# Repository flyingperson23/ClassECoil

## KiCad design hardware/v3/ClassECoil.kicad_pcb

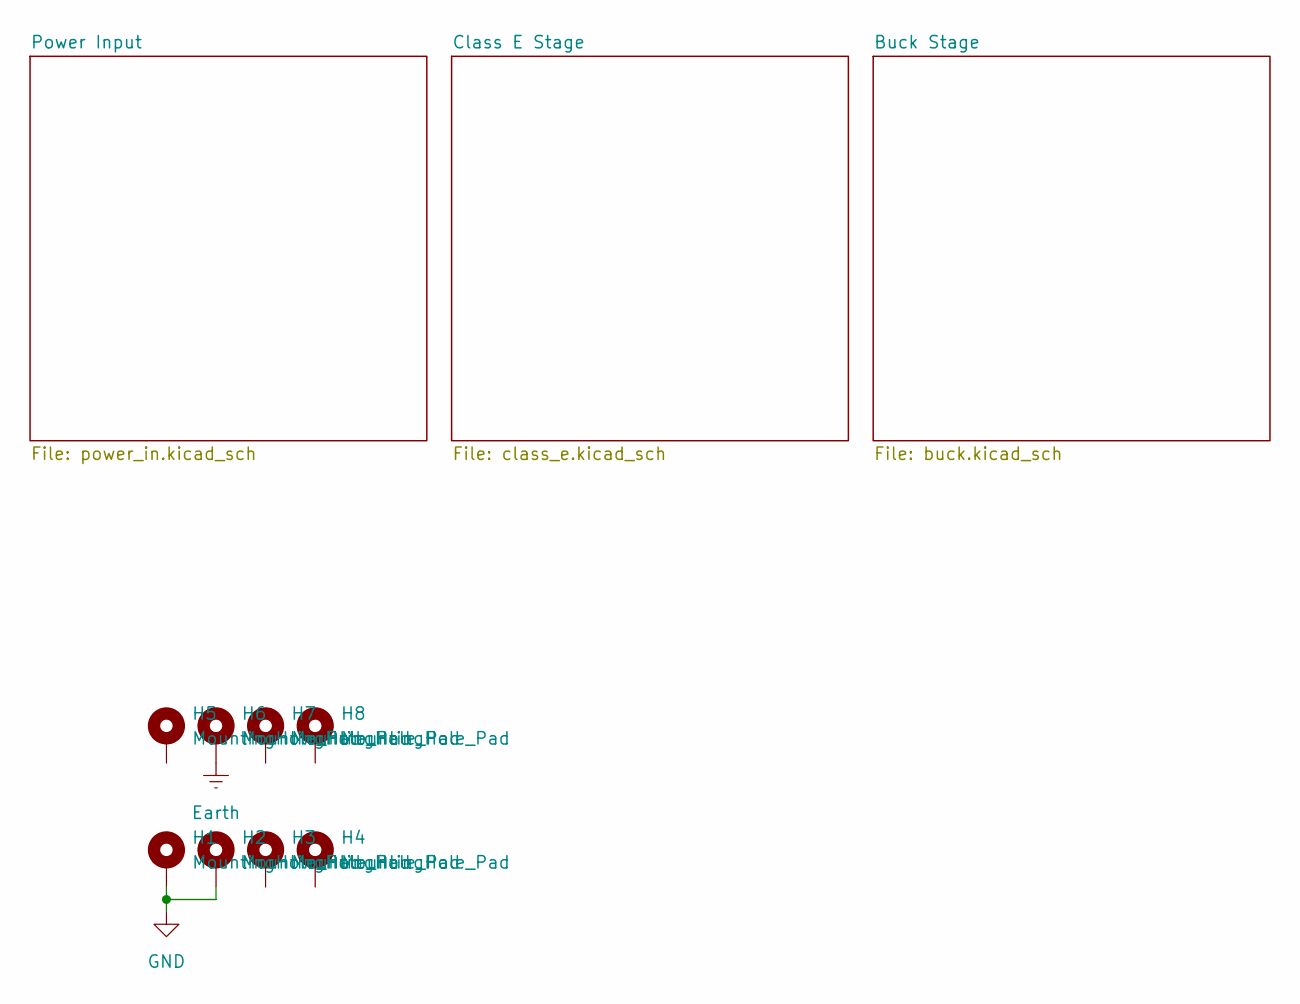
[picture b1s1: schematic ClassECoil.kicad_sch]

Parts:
H1, H2, H3, H4, H5, H6, H7, H8: MountingHole_Pad; MountingHole_3.2mm_M3_Pad_Via

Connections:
Earth: H6.1; also elsewhere on the board
GND: H1.1, H2.1; also elsewhere on the board

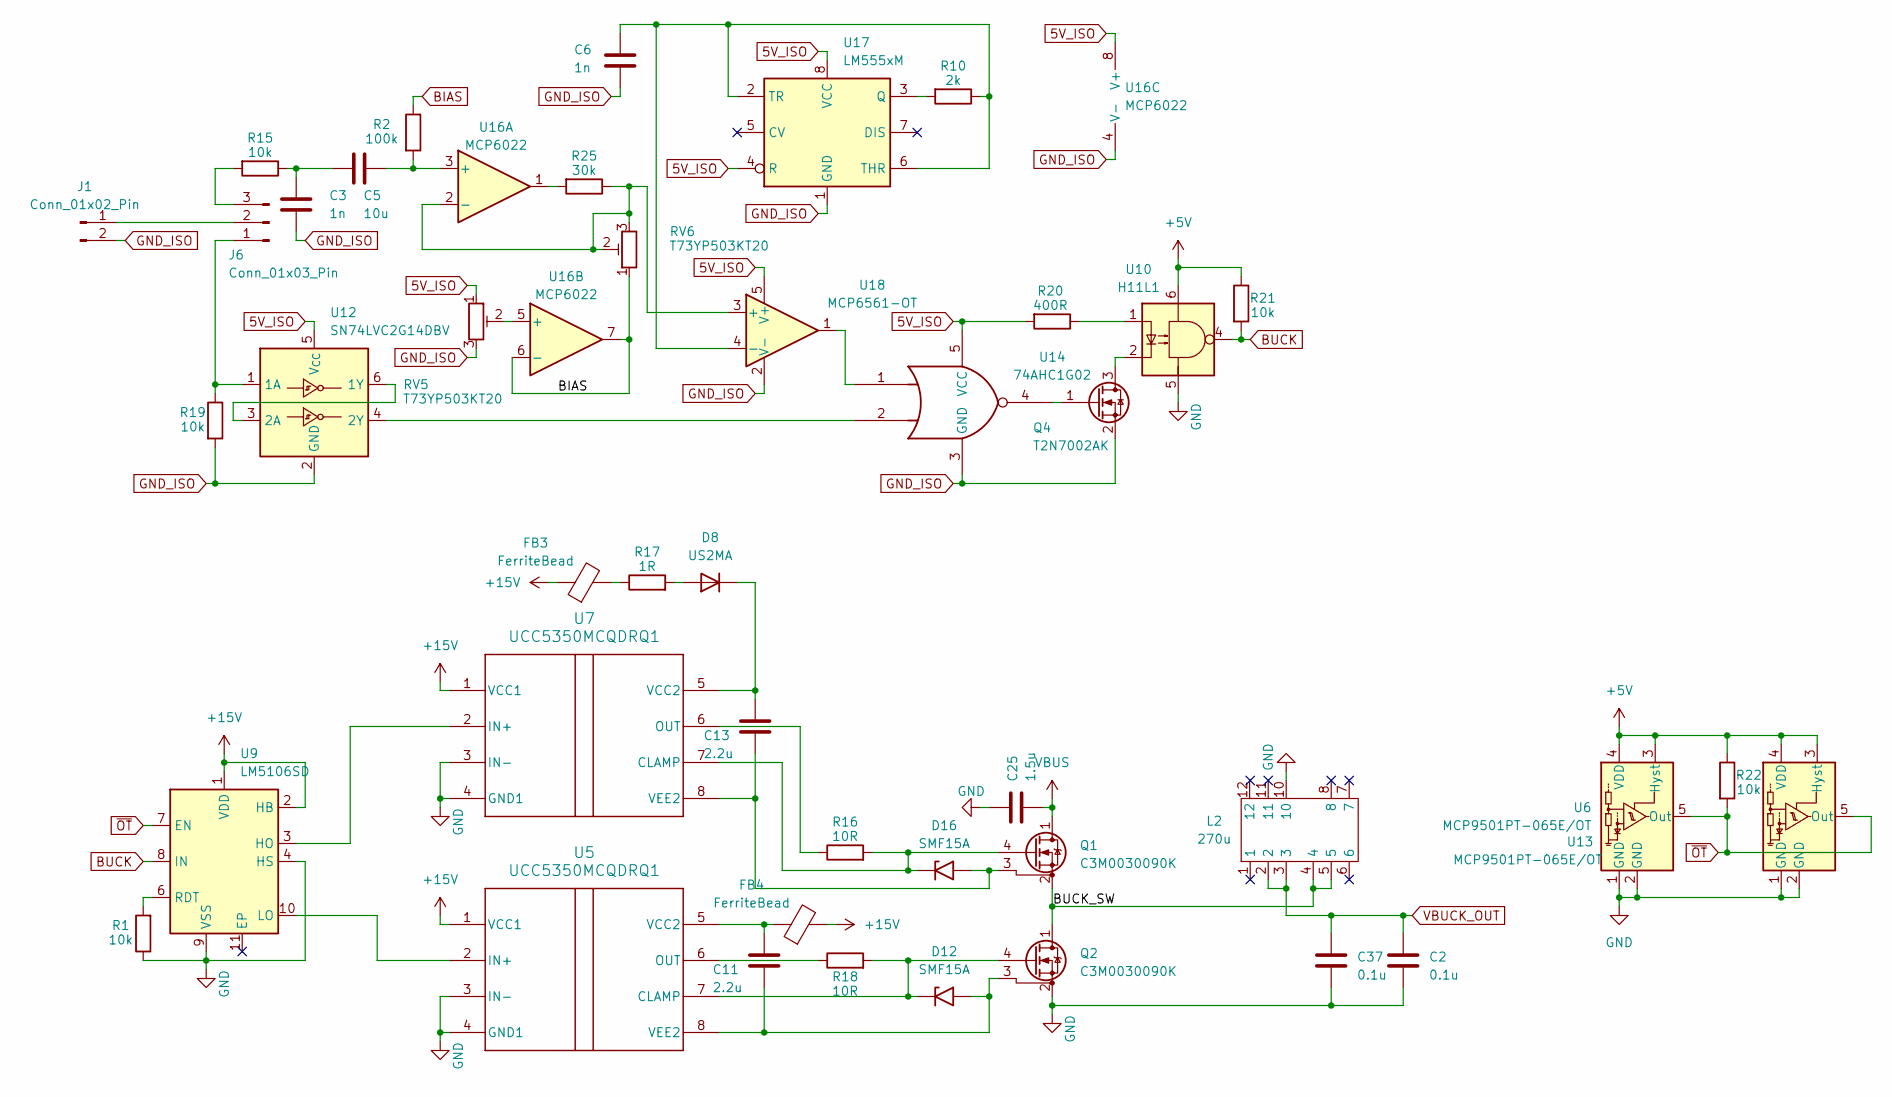
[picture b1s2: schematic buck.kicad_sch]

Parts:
C2, C37: 0.1u; C_Rect_L26.5mm_W8.5mm_P22.50mm_MKS4; MPN MKP1O131005F00KYSD
C3, C6: 1n; C_0805_2012Metric
C5: 10u; C_0805_2012Metric
C11, C13: 2.2u; C_0805_2012Metric
C25: 1.5u; C_Rect_L26.5mm_W8.5mm_P22.50mm_MKS4; MPN MKP1O131005F00KYSD
D8: US2MA; D_SMA
D12, D16: SMF15A; D_SMF
FB3, FB4: FerriteBead; L_0805_2012Metric
J1: Conn_01x02_Pin; Molex_KK-254_AE-6410-02A_1x02_P2.54mm_Vertical
J6: Conn_01x03_Pin; PinHeader_1x03_P2.54mm_Vertical
L2: 270u; 750319521
Q1, Q2: C3M0030090K; TO-247-4_Horizontal_TabUp
Q4: T2N7002AK; SOT-23
R1, R15, R19, R21, R22: 10k; R_0805_2012Metric
R2: 100k; R_0805_2012Metric
R10: 2k; R_0805_2012Metric
R16, R18: 10R; R_0805_2012Metric
R17: 1R; R_0805_2012Metric
R20: 400R; R_0805_2012Metric
R25: 30k; R_0805_2012Metric
RV5, RV6: T73YP503KT20; Potentiometer_Vishay_T73YP_Vertical
U5, U7: UCC5350MCQDRQ1; SOIC-8_3.9x4.9mm_P1.27mm
U6, U13: MCP9501PT-065E/OT; SOT-23-5
U9: LM5106SD; VSSOP-10_3x3mm_P0.5mm
U10: H11L1; DIP-6_W7.62mm
U12: SN74LVC2G14DBV; SOT-23-6
U14: 74AHC1G02; SOT-23-5
U16: MCP6022; SOIC-8_3.9x4.9mm_P1.27mm
U17: LM555xM; SOIC-8_3.9x4.9mm_P1.27mm
U18: MCP6561-OT; SOT-23-5

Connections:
5V_ISO: R20.2, RV5.1, U12.5 (V_{CC}), U14.5 (VCC), U16.8 (V+), U17.4 (R), U17.8 (VCC), U18.5 (V+); also elsewhere on the board
+5V: R21.1, R22.1, U6.3 (Hyst), U6.4 (VDD), U10.6, U13.3 (Hyst), U13.4 (VDD); also elsewhere on the board
+15V: FB3.1, FB4.2, U5.1 (VCC1), U7.1 (VCC1), U9.1 (VDD), U9.2 (HB); also elsewhere on the board
/Buck Stage/BUCK_SW: L2.4, L2.5, Q1.2 (S), Q2.1 (D)
BIAS: R2.1, RV6.1, U16.6 (-), U16.7
BUCK: R21.2, U9.8 (IN), U10.4
GND: C2.2, C25.1, C37.2, L2.10, Q2.2 (S), R1.1, U5.3 (IN-), U5.4 (GND1), U6.1 (GND), U6.2 (GND), U7.3 (IN-), U7.4 (GND1), U9.4 (HS), U9.9 (VSS), U10.5, U13.1 (GND), U13.2 (GND); also elsewhere on the board
GND_ISO: C3.2, C6.2, J1.2, Q4.2 (S), R19.2, RV5.3, U12.2 (GND), U14.3 (GND), U16.4 (V-), U17.1 (GND), U18.2 (V-); also elsewhere on the board
unnamed: C3.1, C5.1, R15.1
unnamed: D8.2 (A), R17.2
unnamed: C13.2, D8.1 (K), U7.5 (VCC2)
unnamed: D12.1 (A1), Q2.4 (G), R18.2, U5.7 (CLAMP)
unnamed: C11.1, D12.2 (A2), Q2.3 (DS), U5.8 (VEE2)
unnamed: D16.1 (A1), Q1.4 (G), R16.2, U7.7 (CLAMP)
unnamed: C13.1, D16.2 (A2), Q1.3 (DS), U7.8 (VEE2)
unnamed: FB3.2, R17.1
unnamed: J1.1, J6.2
unnamed: J6.1, R19.1, U12.1 (1A)
unnamed: J6.3, R15.2
unnamed: Q4.3 (D), U10.2
unnamed: Q4.1 (G), U14.4
unnamed: R20.1, U10.1
unnamed: R25.2, U16.1
unnamed: U5.2 (IN+), U9.10 (LO)
unnamed: R18.1, U5.6 (OUT)
unnamed: C11.2, FB4.1, U5.5 (VCC2)
unnamed: U7.2 (IN+), U9.3 (HO)
unnamed: R16.1, U7.6 (OUT)
unnamed: R1.2, U9.6 (RDT)
unnamed: U12.3 (2A), U12.6 (1Y)
unnamed: U12.4 (2Y), U14.2
unnamed: U14.1, U18.1
unnamed: C5.2, R2.2, U16.3 (+)
unnamed: R25.1, RV6.2, RV6.3, U16.2 (-), U18.3 (+)
unnamed: RV5.2, U16.5 (+)
unnamed: R10.2, U17.3 (Q)
unnamed: C6.1, R10.1, U17.2 (TR), U17.6 (THR), U18.4 (-)
VBUCK_OUT: C2.1, C37.1, L2.2, L2.3; also elsewhere on the board
VBUS: C25.2, Q1.1 (D); also elsewhere on the board
~OT: R22.2, U6.5 (Out), U9.7 (EN), U13.5 (Out)

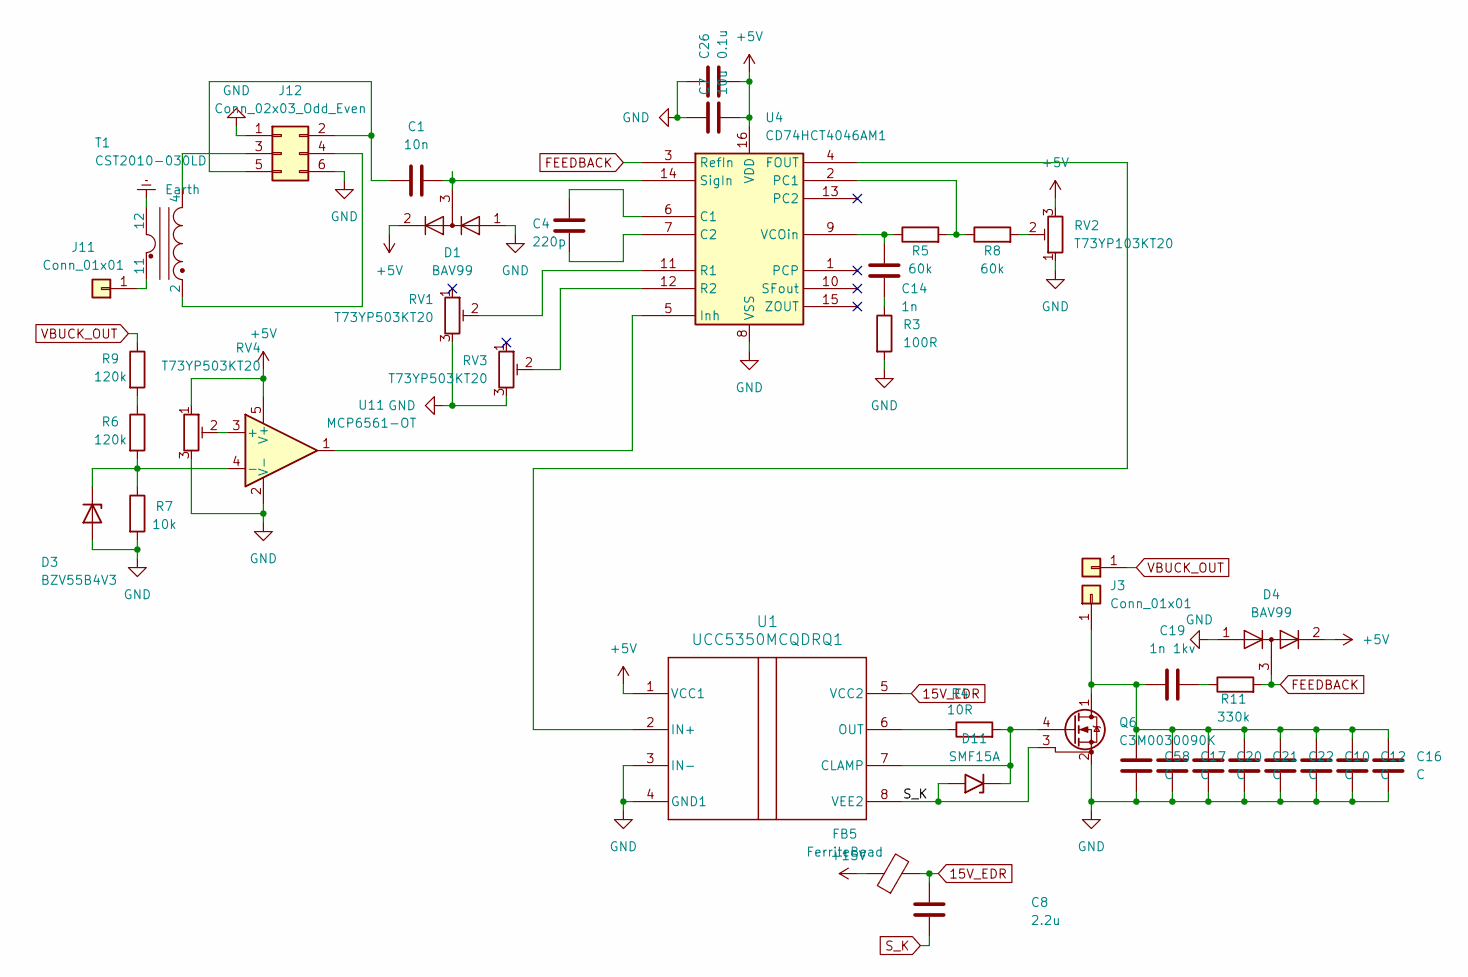
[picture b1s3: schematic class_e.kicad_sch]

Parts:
C1: 10n; C_0805_2012Metric
C4: 220p; C_0805_2012Metric
C7: 10u; C_0805_2012Metric
C8: 2.2u; C_0805_2012Metric
C10, C12, C16, C17, C20, C21, C22, C58: C; C_1210_3225Metric
C14: 1n; C_0805_2012Metric
C19: 1n 1kv; C_0805_2012Metric
C26: 0.1u; C_0805_2012Metric
D1, D4: BAV99; SOT-23
D3: BZV55B4V3; D_MiniMELF
D11: SMF15A; D_SMF
FB5: FerriteBead; L_0805_2012Metric
J2, J3, J11: Conn_01x01; SPADE_726386-2
J12: Conn_02x03_Odd_Even; PinSocket_2x03_P2.54mm_Vertical
Q6: C3M0030090K; TO-247-4_Horizontal_TabUp
R3: 100R; R_0805_2012Metric
R4: 10R; R_0805_2012Metric
R5, R8: 60k; R_0805_2012Metric
R6, R9: 120k; R_0805_2012Metric
R7: 10k; R_0805_2012Metric
R11: 330k; R_0805_2012Metric
RV1, RV3, RV4: T73YP503KT20; Potentiometer_Vishay_T73YP_Vertical
RV2: T73YP103KT20; Potentiometer_Vishay_T73YP_Vertical
T1: CST2010-030LD; Transformer_Coilcraft_CST2010
U1: UCC5350MCQDRQ1; SOIC-8_3.9x4.9mm_P1.27mm
U4: CD74HCT4046AM1; SOIC-16_4.55x10.3mm_P1.27mm
U11: MCP6561-OT; SOT-23-5

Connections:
15V_EDR: C8.1, FB5.2, U1.5 (VCC2)
+5V: C7.1, C26.1, D1.2 (A), D4.2 (A), RV2.3, RV4.1, U1.1 (VCC1), U4.16 (VDD), U11.5 (V+); also elsewhere on the board
+15V: FB5.1; also elsewhere on the board
Earth: T1.12; also elsewhere on the board
FEEDBACK: D4.3 (K), R11.2, U4.3 (RefIn)
GND: C7.2, C10.2, C12.2, C16.2, C17.2, C20.2, C21.2, C22.2, C26.2, C58.2, D1.1 (K), D3.2 (A), D4.1 (K), J12.1, J12.6, Q6.2 (S), R3.2, R7.2, RV1.3, RV2.1, RV3.3, RV4.3, U1.3 (IN-), U1.4 (GND1), U4.8 (VSS), U11.2 (V-); also elsewhere on the board
unnamed: C14.2, R3.1
unnamed: C19.2, R11.1
unnamed: D3.1 (K), R6.2, R7.1, U11.4 (-)
unnamed: D11.1 (A1), Q6.4 (G), R4.2, U1.7 (CLAMP)
unnamed: C10.1, C12.1, C16.1, C17.1, C19.1, C20.1, C21.1, C22.1, C58.1, J3.1, Q6.1 (D)
unnamed: J11.1, T1.11
unnamed: C1.1, J12.2, J12.5
unnamed: J12.3, T1.4
unnamed: J12.4, T1.2
unnamed: R6.1, R9.2
unnamed: R8.2, RV2.2
unnamed: U1.2 (IN+), U4.4 (FOUT)
unnamed: R4.1, U1.6 (OUT)
unnamed: C4.1, U4.6 (C1)
unnamed: C4.2, U4.7 (C2)
unnamed: U4.5 (Inh), U11.1
unnamed: R5.2, R8.1, U4.2 (PC1)
unnamed: RV1.2, U4.11 (R1)
unnamed: RV3.2, U4.12 (R2)
unnamed: C1.2, D1.3 (K), U4.14 (SigIn)
unnamed: C14.1, R5.1, U4.9 (VCOin)
unnamed: RV4.2, U11.3 (+)
S_K: C8.2, D11.2 (A2), Q6.3 (DS), U1.8 (VEE2)
VBUCK_OUT: J2.1, R9.1; also elsewhere on the board

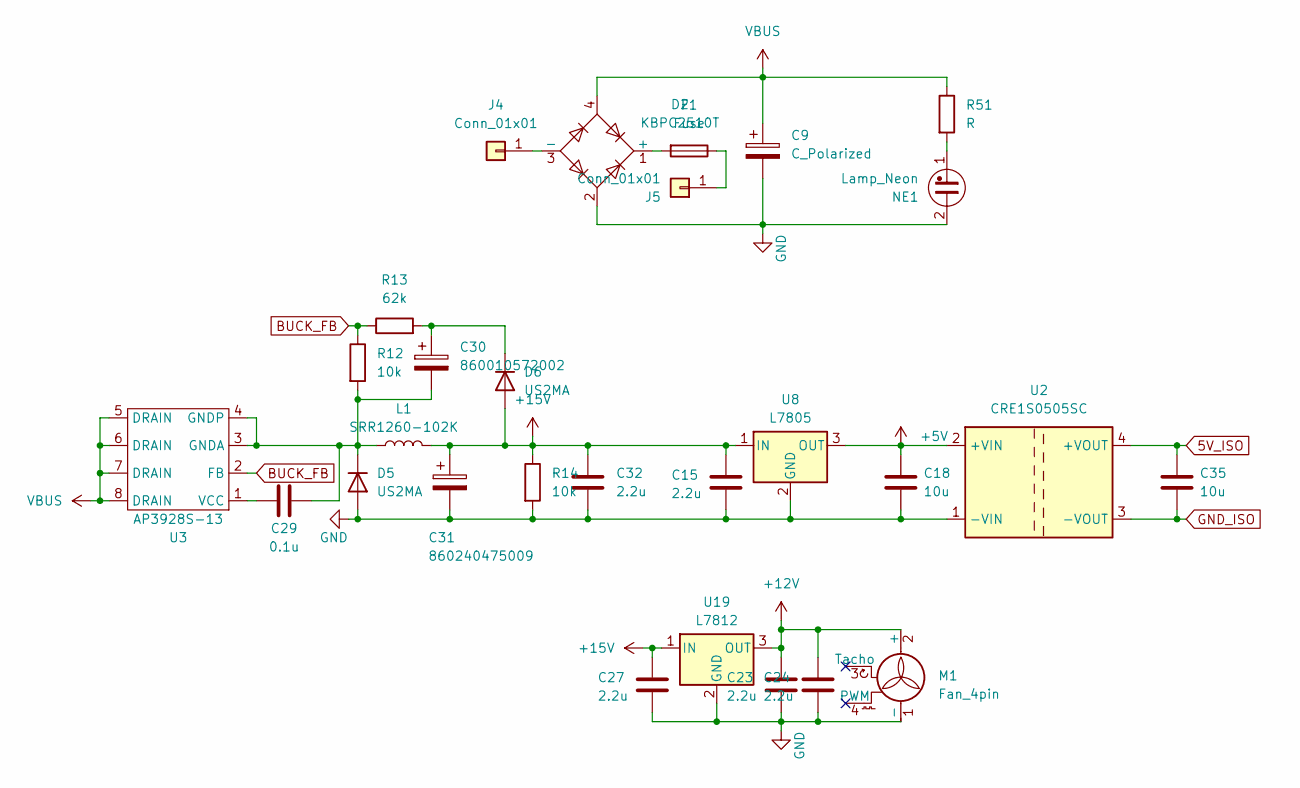
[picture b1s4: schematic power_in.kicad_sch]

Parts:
C9: C_Polarized; CP_Radial_D35.0mm_P10.00mm_SnapIn
C15, C23, C24, C27, C32: 2.2u; C_0805_2012Metric
C18, C35: 10u; C_0805_2012Metric
C29: 0.1u; C_0805_2012Metric
C30: 860010572002; CP_Radial_D5.0mm_P2.00mm
C31: 860240475009; CP_Radial_D10.0mm_P5.00mm
D2: KBPC2510T; Diode_Bridge_GeneSiC_KBPC_T
D5, D6: US2MA; D_SMA
F1: Fuse; Fuseholder_Clip-6.3x32mm_Littelfuse_102071_Inline_P34.70x7.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
J4, J5: Conn_01x01; SPADE_726386-2
L1: SRR1260-102K; L_Bourns_SRR1260
M1: Fan_4pin; FanPinHeader_1x04_P2.54mm_Vertical
NE1: Lamp_Neon; NEON-A1A
R12, R14: 10k; R_0805_2012Metric
R13: 62k; R_0805_2012Metric
R51: R; R_Axial_DIN0207_L6.3mm_D2.5mm_P2.54mm_Vertical
U2: CRE1S0505SC; Converter_DCDC_Murata_CRE1xxxxxxSC_THT
U3: AP3928S-13; SO-8_3.9x4.9mm_P1.27mm
U8: L7805; TO-220-3_Vertical
U19: L7812; TO-220-3_Horizontal_TabDown

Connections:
5V_ISO: C35.2, U2.4 (+VOUT); also elsewhere on the board
+5V: C18.2, U2.2 (+VIN), U8.3 (OUT); also elsewhere on the board
+12V: C23.1, C24.1, M1.2 (+), U19.3 (OUT)
+15V: C15.1, C27.1, C31.1, C32.1, D6.2 (A), L1.2, R14.1, U8.1 (IN), U19.1 (IN); also elsewhere on the board
BUCK_FB: R12.1, R13.1, U3.2 (FB)
GND: C9.2, C15.2, C18.1, C23.2, C24.2, C27.2, C31.2, C32.2, D2.2, D5.2 (A), M1.1 (-), NE1.2, R14.2, U2.1 (-VIN), U8.2 (GND), U19.2 (GND); also elsewhere on the board
GND_ISO: C35.1, U2.3 (-VOUT); also elsewhere on the board
unnamed: D2.1 (+), F1.2
unnamed: D2.3 (-), J4.1
unnamed: C29.1, C30.2, D5.1 (K), L1.1, R12.2, U3.3 (GNDA), U3.4 (GNDP)
unnamed: C30.1, D6.1 (K), R13.2
unnamed: F1.1, J5.1
unnamed: NE1.1, R51.2
unnamed: C29.2, U3.1 (VCC)
VBUS: C9.1, D2.4, R51.1, U3.5 (DRAIN), U3.6 (DRAIN), U3.7 (DRAIN), U3.8 (DRAIN); also elsewhere on the board

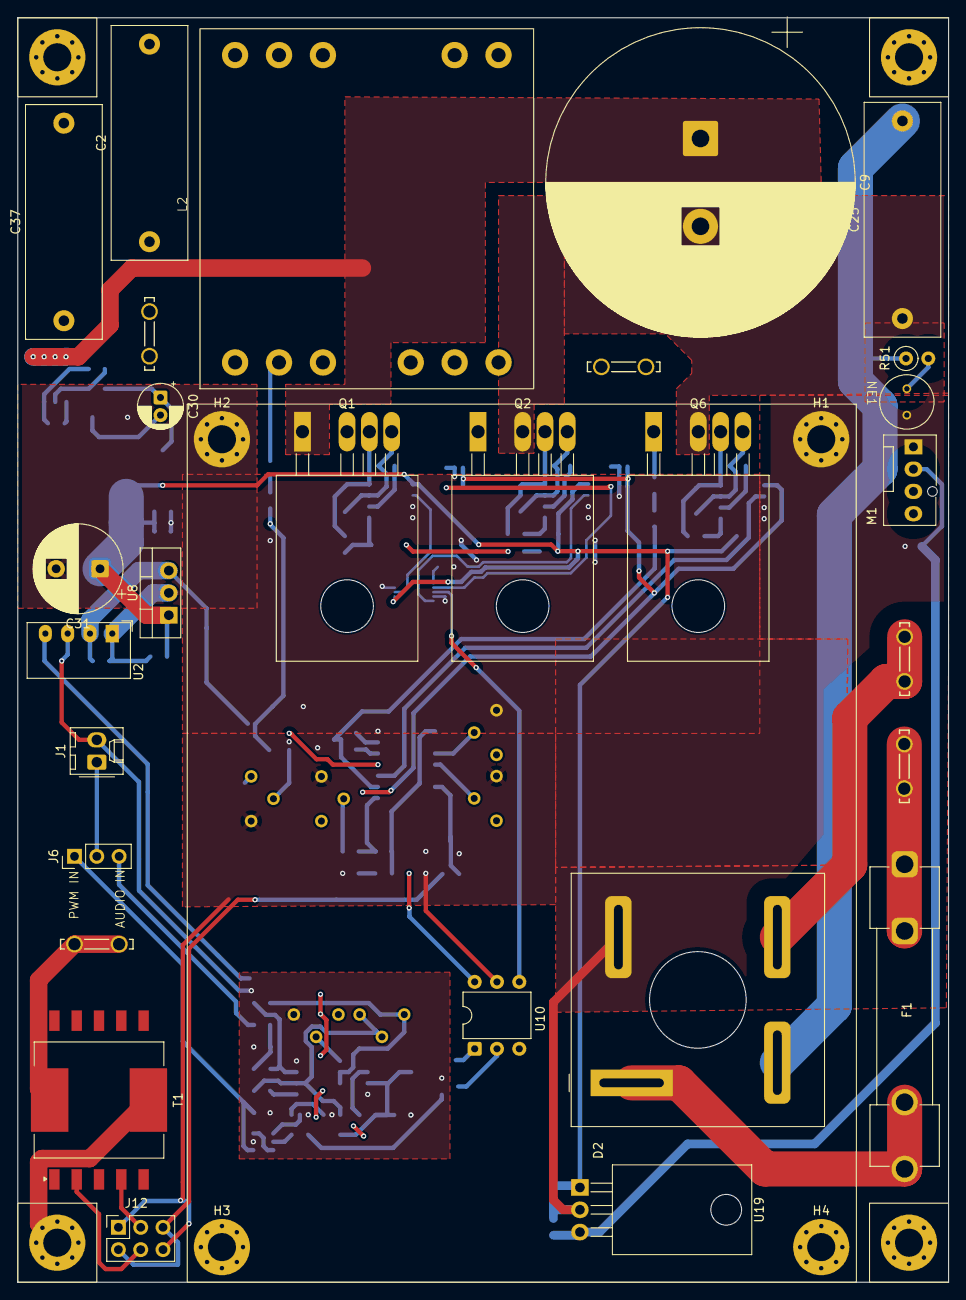
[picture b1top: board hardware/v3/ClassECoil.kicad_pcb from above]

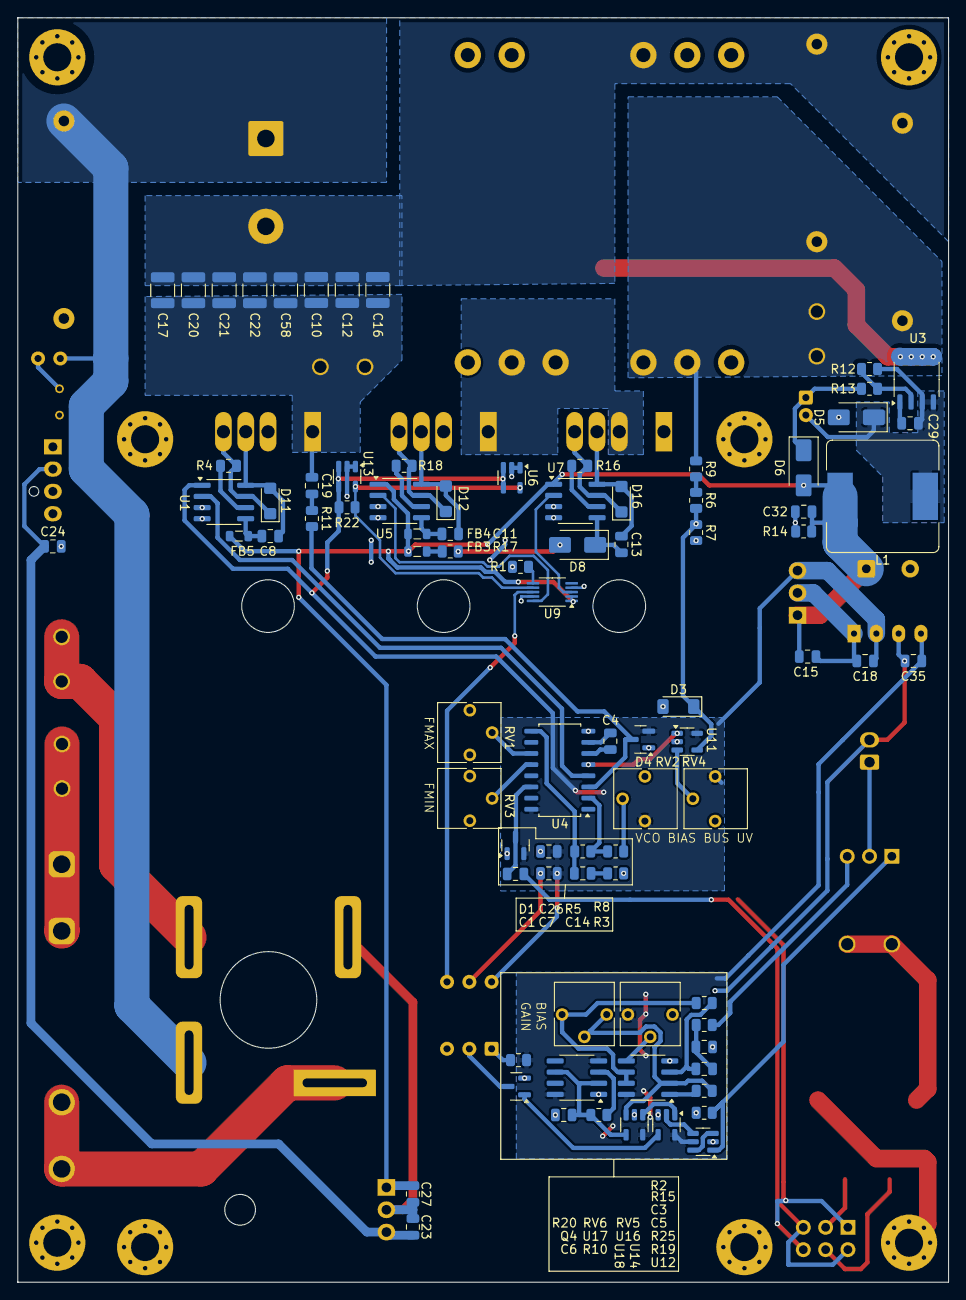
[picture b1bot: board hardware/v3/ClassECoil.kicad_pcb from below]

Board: 2 copper layers, 106.0 x 144.0 mm, 120 parts (84 on the bottom side), 75 nets.

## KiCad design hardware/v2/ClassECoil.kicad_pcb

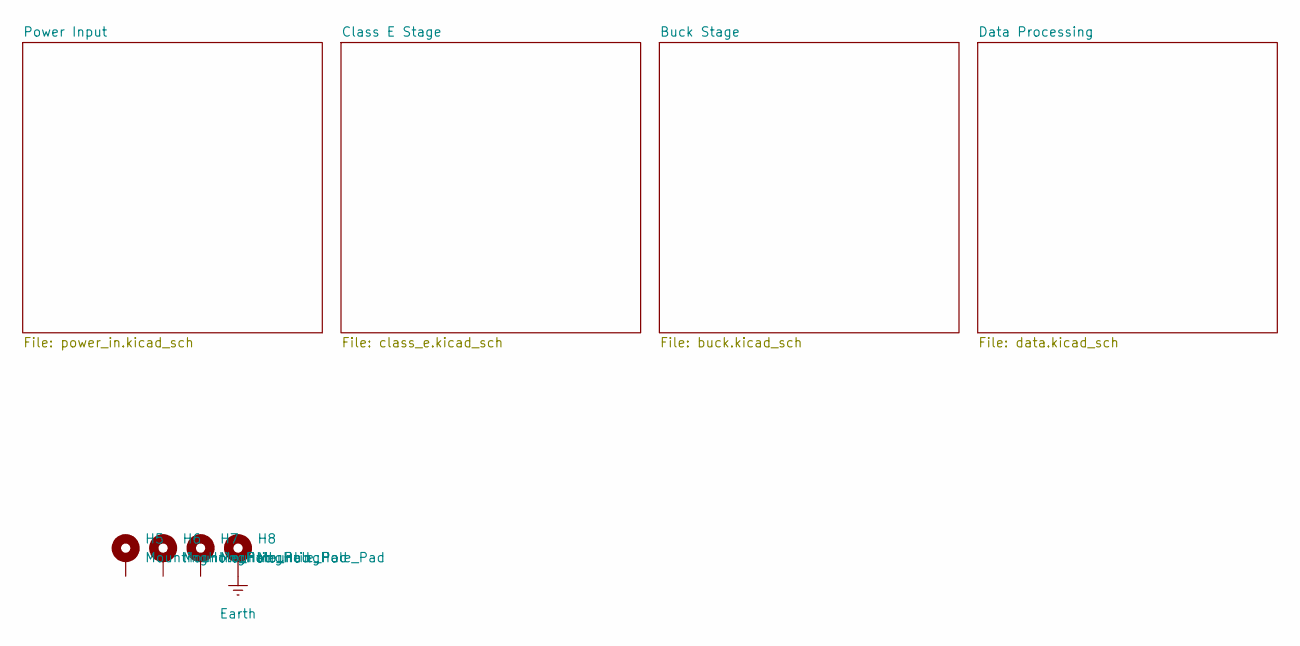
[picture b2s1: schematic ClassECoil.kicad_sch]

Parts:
H5, H6, H7, H8: MountingHole_Pad; MountingHole_3.2mm_M3_Pad_Via

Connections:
Earth: H8.1; also elsewhere on the board

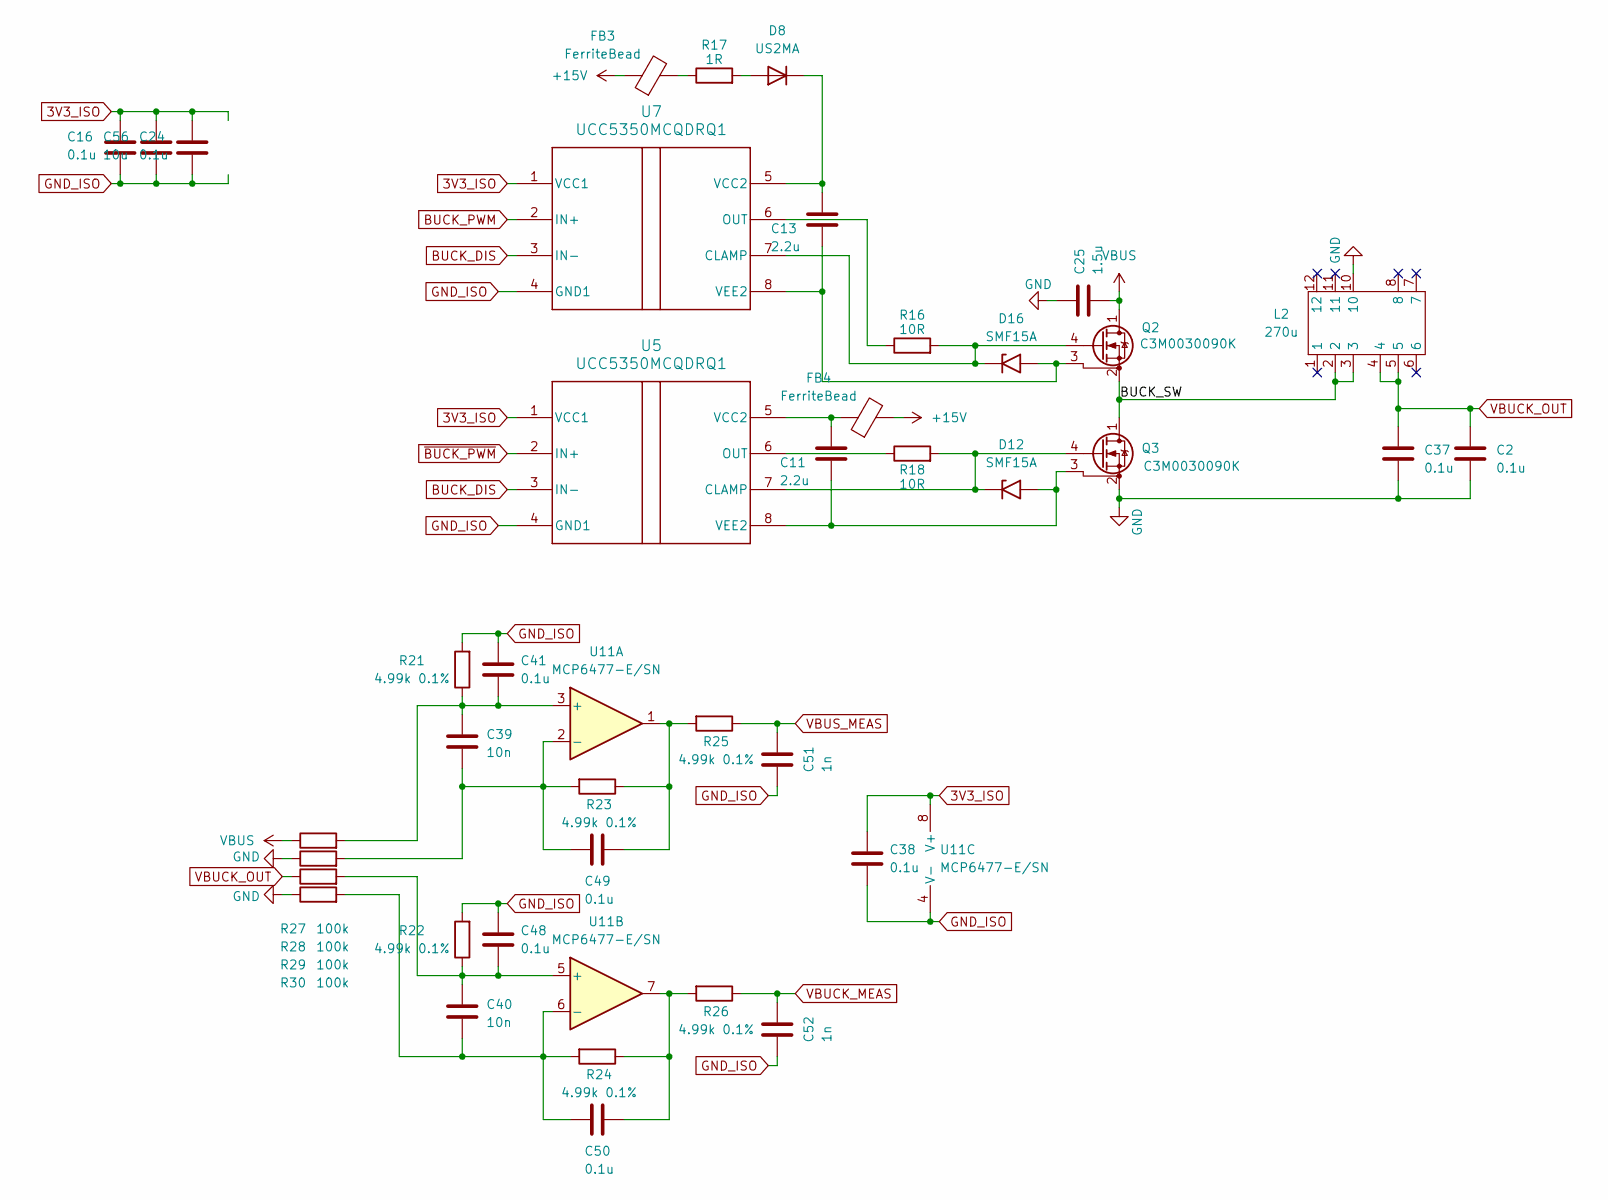
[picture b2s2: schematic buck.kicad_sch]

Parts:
C2, C37: 0.1u; C_Rect_L26.5mm_W8.5mm_P22.50mm_MKS4; MPN MKP1O131005F00KYSD
C11, C13: 2.2u; C_0805_2012Metric
C16, C24, C38, C41, C48, C49, C50: 0.1u; C_0805_2012Metric
C25: 1.5u; C_Rect_L26.5mm_W8.5mm_P22.50mm_MKS4; MPN MKP1O131005F00KYSD
C39, C40: 10n; C_0805_2012Metric
C51, C52: 1n; C_0805_2012Metric
C56: 10u; C_0805_2012Metric
D8: US2MA; D_SMA
D12, D16: SMF15A; D_SMF
FB3, FB4: FerriteBead; L_0805_2012Metric
L2: 270u; 750319521
Q2, Q3: C3M0030090K; TO-247-4_Vertical
R16, R18: 10R; R_0805_2012Metric
R17: 1R; R_0805_2012Metric
R21, R22, R23, R24, R25, R26: 4.99k 0.1%; R_0805_2012Metric
R27, R28, R29, R30: 100k; R_2512_6332Metric
U5, U7: UCC5350MCQDRQ1; SOIC-8_3.9x4.9mm_P1.27mm
U11: MCP6477-E/SN; SOIC-8_3.9x4.9mm_P1.27mm

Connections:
3V3_ISO: C16.1, C24.1, C38.1, C56.1, U5.1 (VCC1), U7.1 (VCC1), U11.8 (V+); also elsewhere on the board
+15V: FB3.1, FB4.2; also elsewhere on the board
/Buck Stage/BUCK_SW: L2.2, L2.3, Q2.2 (S), Q3.1 (D)
BUCK_DIS: U5.3 (IN-), U7.3 (IN-); also elsewhere on the board
BUCK_PWM: U7.2 (IN+); also elsewhere on the board
GND: C2.2, C25.1, C37.2, L2.10, Q3.2 (S), R28.1, R30.1; also elsewhere on the board
GND_ISO: C16.2, C24.2, C38.2, C41.1, C48.1, C51.2, C52.2, C56.2, R21.2, R22.2, U5.4 (GND1), U7.4 (GND1), U11.4 (V-); also elsewhere on the board
unnamed: C49.1, R23.1, R25.2, U11.1
unnamed: C50.1, R24.1, R26.2, U11.7
unnamed: D8.2 (A), R17.2
unnamed: C13.2, D8.1 (K), U7.5 (VCC2)
unnamed: D12.1 (A1), Q3.4 (G), R18.2, U5.7 (CLAMP)
unnamed: C11.1, D12.2 (A2), Q3.3 (DS), U5.8 (VEE2)
unnamed: D16.1 (A1), Q2.4 (G), R16.2, U7.7 (CLAMP)
unnamed: C13.1, D16.2 (A2), Q2.3 (DS), U7.8 (VEE2)
unnamed: FB3.2, R17.1
unnamed: R18.1, U5.6 (OUT)
unnamed: C11.2, FB4.1, U5.5 (VCC2)
unnamed: R16.1, U7.6 (OUT)
unnamed: C39.1, C41.2, R21.1, R27.2, U11.3 (+)
unnamed: C39.2, C49.2, R23.2, R28.2, U11.2 (-)
unnamed: C40.1, C48.2, R22.1, R29.2, U11.5 (+)
unnamed: C40.2, C50.2, R24.2, R30.2, U11.6 (-)
VBUCK_MEAS: C52.1, R26.1; also elsewhere on the board
VBUCK_OUT: C2.1, C37.1, L2.4, L2.5, R29.1; also elsewhere on the board
VBUS: C25.2, Q2.1 (D), R27.1; also elsewhere on the board
VBUS_MEAS: C51.1, R25.1; also elsewhere on the board
~BUCK_PWM: U5.2 (IN+); also elsewhere on the board

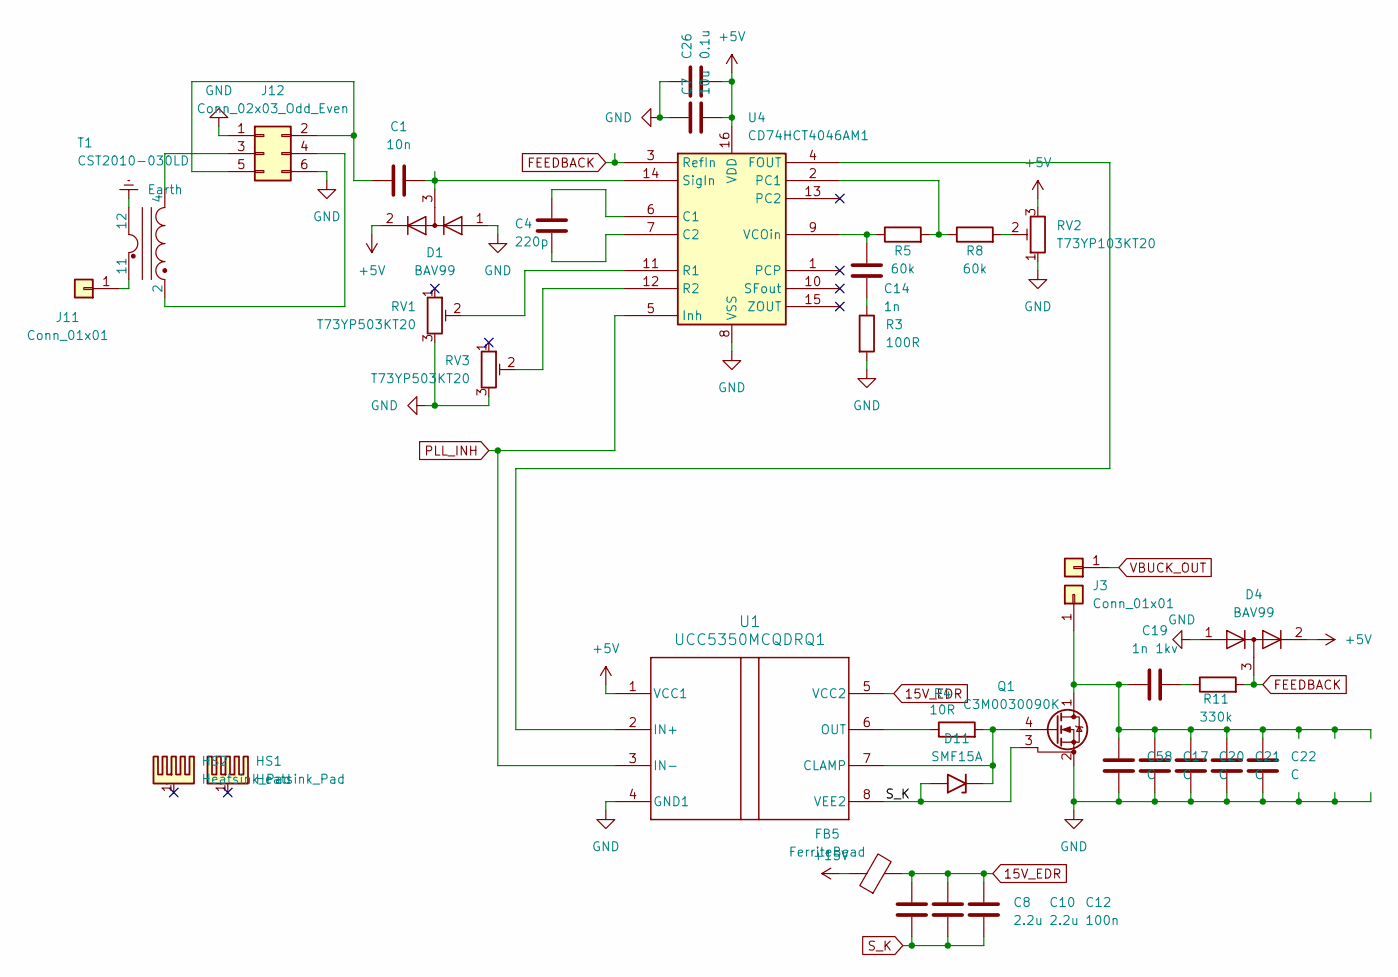
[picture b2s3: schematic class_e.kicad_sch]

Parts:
C1: 10n; C_0805_2012Metric
C4: 220p; C_0805_2012Metric
C7: 10u; C_0805_2012Metric
C8, C10: 2.2u; C_0805_2012Metric
C12: 100n; C_0805_2012Metric
C14: 1n; C_0805_2012Metric
C17, C20, C21, C22, C58: C; C_1210_3225Metric
C19: 1n 1kv; C_0805_2012Metric
C26: 0.1u; C_0805_2012Metric
D1, D4: BAV99; SOT-23
D11: SMF15A; D_SMF
FB5: FerriteBead; L_0805_2012Metric
HS1, HS2: Heatsink_Pad; C40_Half
J2, J3, J11: Conn_01x01; SPADE_726386-2
J12: Conn_02x03_Odd_Even; PinSocket_2x03_P2.54mm_Vertical
Q1: C3M0030090K; TO-247-4_Vertical
R3: 100R; R_0805_2012Metric
R4: 10R; R_0805_2012Metric
R5, R8: 60k; R_0805_2012Metric
R11: 330k; R_0805_2012Metric
RV1, RV3: T73YP503KT20; Potentiometer_Vishay_T73YP_Vertical
RV2: T73YP103KT20; Potentiometer_Vishay_T73YP_Vertical
T1: CST2010-030LD; Transformer_Coilcraft_CST2010
U1: UCC5350MCQDRQ1; SOIC-8_3.9x4.9mm_P1.27mm
U4: CD74HCT4046AM1; SOIC-16_4.55x10.3mm_P1.27mm

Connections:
15V_EDR: C8.1, C10.1, C12.1, FB5.2, U1.5 (VCC2)
+5V: C7.1, C26.1, D1.2 (A), D4.2 (A), RV2.3, U1.1 (VCC1), U4.16 (VDD); also elsewhere on the board
+15V: FB5.1; also elsewhere on the board
Earth: T1.12; also elsewhere on the board
FEEDBACK: D4.3 (K), R11.2, U4.3 (RefIn)
GND: C7.2, C17.2, C20.2, C21.2, C22.2, C26.2, C58.2, D1.1 (K), D4.1 (K), J12.1, J12.6, Q1.2 (S), R3.2, RV1.3, RV2.1, RV3.3, U1.4 (GND1), U4.8 (VSS); also elsewhere on the board
unnamed: C14.2, R3.1
unnamed: C19.2, R11.1
unnamed: D11.1 (A1), Q1.4 (G), R4.2, U1.7 (CLAMP)
unnamed: C17.1, C19.1, C20.1, C21.1, C22.1, C58.1, J3.1, Q1.1 (D)
unnamed: J11.1, T1.11
unnamed: C1.1, J12.2, J12.5
unnamed: J12.3, T1.4
unnamed: J12.4, T1.2
unnamed: R8.2, RV2.2
unnamed: U1.2 (IN+), U4.4 (FOUT)
unnamed: R4.1, U1.6 (OUT)
unnamed: C4.1, U4.6 (C1)
unnamed: C4.2, U4.7 (C2)
unnamed: R5.2, R8.1, U4.2 (PC1)
unnamed: RV1.2, U4.11 (R1)
unnamed: RV3.2, U4.12 (R2)
unnamed: C1.2, D1.3 (K), U4.14 (SigIn)
unnamed: C14.1, R5.1, U4.9 (VCOin)
PLL_INH: U1.3 (IN-), U4.5 (Inh); also elsewhere on the board
S_K: C8.2, C10.2, C12.2, D11.2 (A2), Q1.3 (DS), U1.8 (VEE2)
VBUCK_OUT: J2.1; also elsewhere on the board

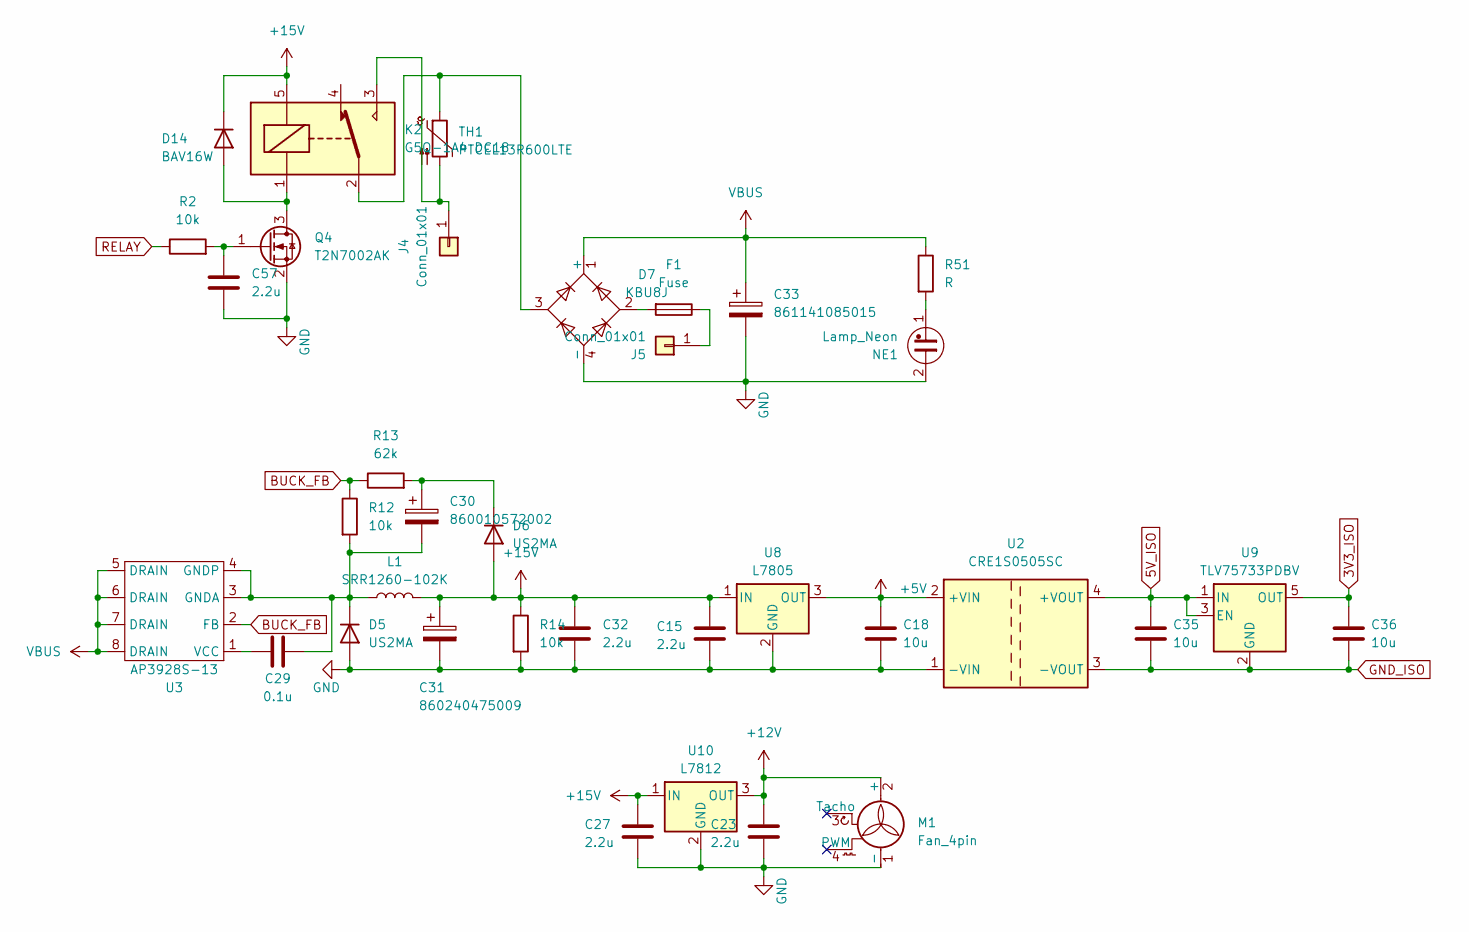
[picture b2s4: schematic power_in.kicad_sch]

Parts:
C15, C23, C27, C32, C57: 2.2u; C_0805_2012Metric
C18, C35, C36: 10u; C_0805_2012Metric
C29: 0.1u; C_0805_2012Metric
C30: 860010572002; CP_Radial_D5.0mm_P2.00mm
C31: 860240475009; CP_Radial_D10.0mm_P5.00mm
C33: 861141085015; CP_Radial_D30.0mm_P10.00mm_SnapIn
D5, D6: US2MA; D_SMA
D7: KBU8J; Diode_Bridge_Vishay_KBU
D14: BAV16W; D_SOD-123
F1: Fuse; Fuseholder_Clip-6.3x32mm_Littelfuse_102071_Inline_P34.70x7.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
J4, J5: Conn_01x01; SPADE_726386-2
K2: G5Q-1A4 DC18; Relay_SPDT_Omron-G5Q-1
L1: SRR1260-102K; L_Bourns_SRR1260
M1: Fan_4pin; FanPinHeader_1x04_P2.54mm_Vertical
NE1: Lamp_Neon; NEON-A1A
Q4: T2N7002AK; SOT-23
R2, R12, R14: 10k; R_0805_2012Metric
R13: 62k; R_0805_2012Metric
R51: R; R_Axial_DIN0207_L6.3mm_D2.5mm_P2.54mm_Vertical
TH1: PTCEL13R600LTE; THERMISTOR_PTCEL13_5MM_VIS
U2: CRE1S0505SC; Converter_DCDC_Murata_CRE1xxxxxxSC_THT
U3: AP3928S-13; SO-8_3.9x4.9mm_P1.27mm
U8: L7805; TO-220-3_Vertical
U9: TLV75733PDBV; SOT-23-5
U10: L7812; TO-220-3_Vertical

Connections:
3V3_ISO: C36.2, U9.5 (OUT); also elsewhere on the board
5V_ISO: C35.2, U2.4 (+VOUT), U9.1 (IN), U9.3 (EN); also elsewhere on the board
+5V: C18.2, U2.2 (+VIN), U8.3 (OUT); also elsewhere on the board
+12V: C23.1, M1.2 (+), U10.3 (OUT)
+15V: C15.1, C27.1, C31.1, C32.1, D6.2 (A), D14.1 (K), K2.5, L1.2, R14.1, U8.1 (IN), U10.1 (IN); also elsewhere on the board
BUCK_FB: R12.1, R13.1, U3.2 (FB)
GND: C15.2, C18.1, C23.2, C27.2, C31.2, C32.2, C33.2, C57.2, D5.2 (A), D7.4 (-), M1.1 (-), NE1.2, Q4.2 (S), R14.2, U2.1 (-VIN), U8.2 (GND), U10.2 (GND); also elsewhere on the board
GND_ISO: C35.1, C36.1, U2.3 (-VOUT), U9.2 (GND); also elsewhere on the board
unnamed: C29.1, C30.2, D5.1 (K), L1.1, R12.2, U3.3 (GNDA), U3.4 (GNDP)
unnamed: C30.1, D6.1 (K), R13.2
unnamed: D7.2, F1.2
unnamed: D7.3, K2.2, TH1.1
unnamed: D14.2 (A), K2.1, Q4.3 (D)
unnamed: J4.1, K2.3, TH1.2
unnamed: F1.1, J5.1
unnamed: NE1.1, R51.2
unnamed: C57.1, Q4.1 (G), R2.2
unnamed: C29.2, U3.1 (VCC)
RELAY: R2.1; also elsewhere on the board
VBUS: C33.1, D7.1 (+), R51.1, U3.5 (DRAIN), U3.6 (DRAIN), U3.7 (DRAIN), U3.8 (DRAIN); also elsewhere on the board

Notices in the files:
software/Core/Src/stm32g4xx_hal_msp.c:
Copyright (c) 2025 STMicroelectronics.
All rights reserved.
This software is licensed under terms that can be found in the LICENSE file
